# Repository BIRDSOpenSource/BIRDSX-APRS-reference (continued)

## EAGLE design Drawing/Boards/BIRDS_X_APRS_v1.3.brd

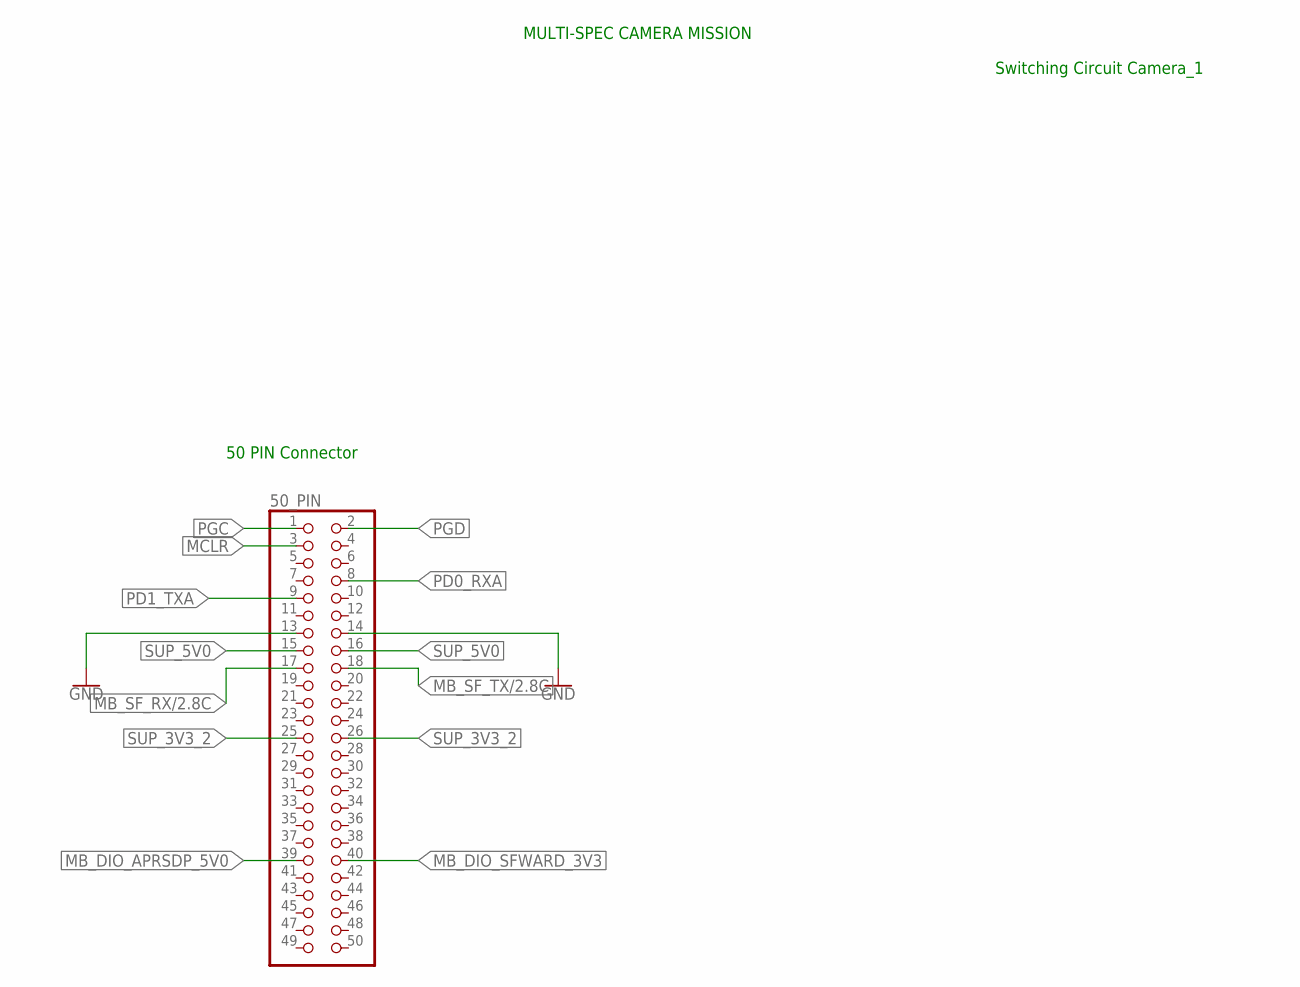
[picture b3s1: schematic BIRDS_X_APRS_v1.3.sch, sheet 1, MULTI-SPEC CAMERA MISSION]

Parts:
50_PIN: PINHD-2X25_2.00; 2X25M

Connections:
GND: 50_PIN.13, 50_PIN.14; also elsewhere on the board
MB_DIO_APRSDP_5V0: 50_PIN.39; also elsewhere on the board
MB_DIO_SFWARD_3V3: 50_PIN.40; also elsewhere on the board
MB_SF_RX/2.8C: 50_PIN.17
MB_SF_TX/2.8C: 50_PIN.18
MCLR: 50_PIN.3; also elsewhere on the board
PD0_RXA: 50_PIN.8; also elsewhere on the board
PD1_TXA: 50_PIN.9; also elsewhere on the board
PGC: 50_PIN.1; also elsewhere on the board
PGD: 50_PIN.2; also elsewhere on the board
SUP_3V3_2: 50_PIN.25, 50_PIN.26; also elsewhere on the board
SUP_5V0: 50_PIN.15, 50_PIN.16; also elsewhere on the board

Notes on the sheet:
50 PIN Connector
Switching Circuit Camera_1
MULTI-SPEC CAMERA MISSION

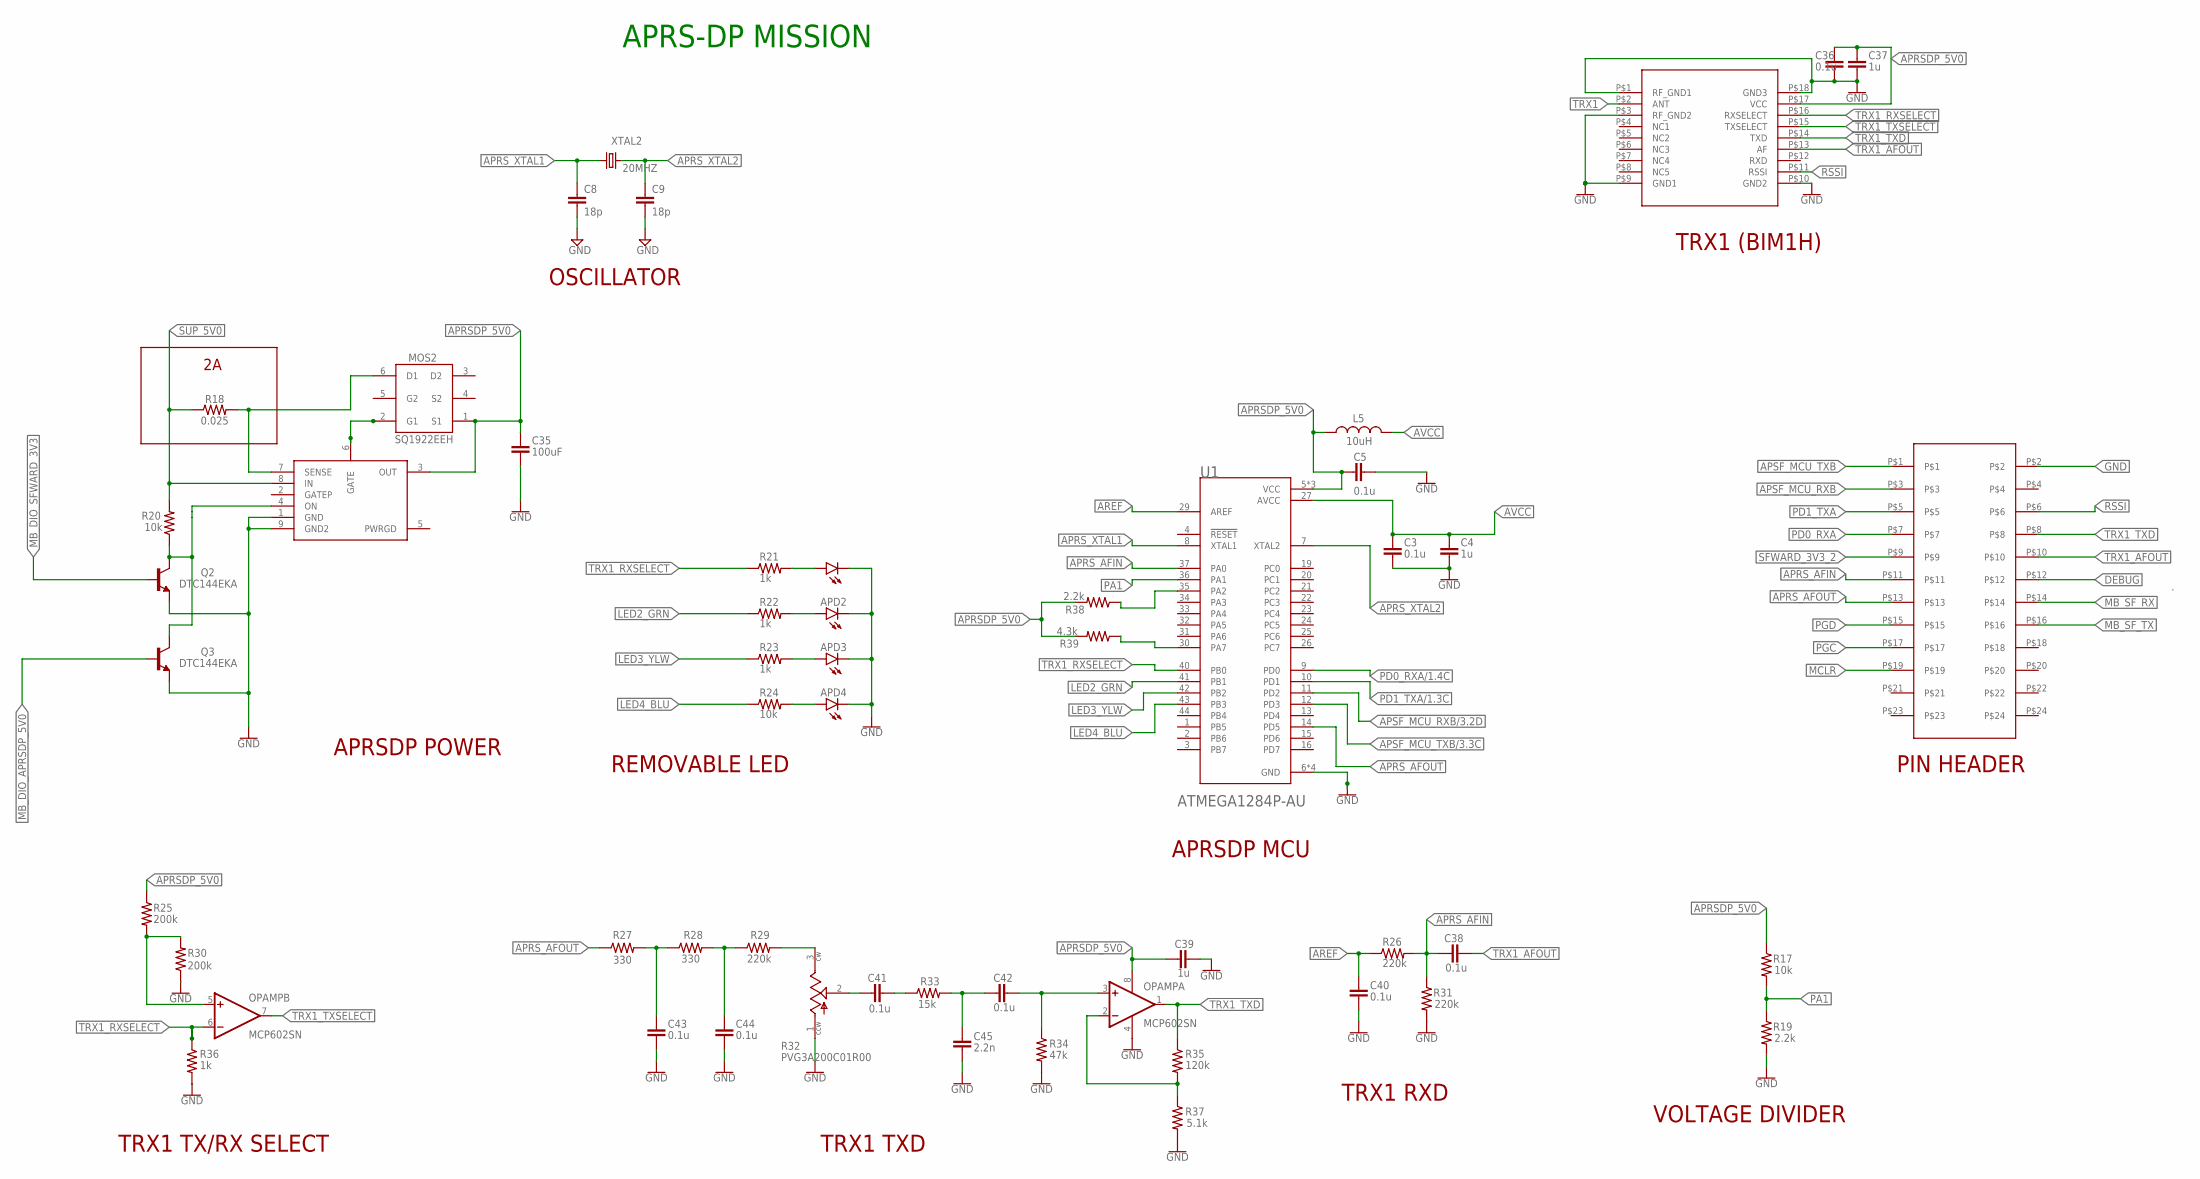
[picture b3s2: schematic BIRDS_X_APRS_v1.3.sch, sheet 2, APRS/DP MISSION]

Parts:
APD1, APD2, APD3, APD4: LEDSML0603; SML0603
C3, C5, C36, C38, C40, C41, C42, C43, C44: 0.1u; C0603
C4, C37, C39: 1u; C0603
C8, C9: 18p; C0805
C35: 100uF; C0805
C45: 2.2n; C0603
JP1: RAB_ACCESS
L5: 10uH; L2012C
MOS2: SQ1922EEH; SOT65P210X110-6N
OPAMP: MCP602SN; SO08
Q2, Q3: DTC144EKA; SOT346-R
R17, R20, R24: 10k; R0603
R18: 0.025; R0805
R19, R38: 2.2k; R0603
R21, R22, R23, R36: 1k; R0603
R25, R30: 200k; R0603
R26, R29, R31: 220k; R0603
R27, R28: 330; R0603
R32: PVG3A200C01R00; TRIM_PVG3A200C01R00
R33: 15k; R0603
R34: 47k; R0603
R35: 120k; R0603
R37: 5.1k; R0603
R39: 4.3k; R0603
TRX1: BIM1H
U1: ATMEGA1284P-AU; QFP80P1200X1200X120-44N
U$1: BIRDS5_LTC4361
XTAL2: 20MHZ; SM49

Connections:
APRSDP_5V0: C5.2, C35.1, C36.1, C37.1, C39.1, L5.1, MOS2.1 (S1), OPAMP.8 (V+), R17.1, R25.1, R38.2, R39.2, TRX1.P$17 (VCC), U1.5 (VCC), U1.17 (VCC), U1.38 (VCC), U$1.3 (OUT)
APRS_AFIN: C38.1, JP1.P$11, R26.2, R31.1, U1.37 (PA0)
APRS_AFOUT: JP1.P$13, R27.1, U1.14 (PD5)
APRS_XTAL1: C8.1, U1.8 (XTAL1), XTAL2.1
APRS_XTAL2: C9.1, U1.7 (XTAL2), XTAL2.2
APSF_MCU_RXB: JP1.P$3; also elsewhere on the board
APSF_MCU_RXB/3.2D: U1.11 (PD2)
APSF_MCU_TXB: JP1.P$1; also elsewhere on the board
APSF_MCU_TXB/3.3C: U1.12 (PD3)
AREF: C40.1, R26.1, U1.29 (AREF)
AVCC: C3.1, C4.1, L5.2, U1.27 (AVCC)
DEBUG: JP1.P$12; also elsewhere on the board
GATE4: MOS2.2 (G1), U$1.6 (GATE)
GND: APD1.C, APD2.C, APD3.C, APD4.C, C3.2, C4.2, C5.1, C8.2, C9.2, C35.2, C36.2, C37.2, C39.2, C40.2, C43.2, C44.2, C45.2, JP1.P$2, OPAMP.4 (V-), Q2.1 (E), Q3.1 (E), R19.2, R30.1, R31.2, R32.1 (CCW), R34.2, R36.2, R37.2, TRX1.P$1 (RF_GND1), TRX1.P$3 (RF_GND2), TRX1.P$9 (GND1), TRX1.P$10 (GND2), TRX1.P$18 (GND3), U1.6 (GND), U1.18 (GND), U1.28 (GND), U1.39 (GND), U$1.1 (GND), U$1.9 (GND2); also elsewhere on the board
LED2_GRN: R22.1, U1.41 (PB1)
LED3_YLW: R23.1, U1.42 (PB2)
LED4_BLU: R24.1, U1.43 (PB3)
MB_DIO_APRSDP_5V0: Q3.2 (B); also elsewhere on the board
MB_DIO_SFWARD_3V3: Q2.2 (B); also elsewhere on the board
MB_SF_RX: JP1.P$14; also elsewhere on the board
MB_SF_TX: JP1.P$16; also elsewhere on the board
MCLR: JP1.P$19; also elsewhere on the board
unnamed: R38.1, U1.35 (PA2)
unnamed: R39.1, U1.30 (PA7)
unnamed: R29.2, R32.3 (CW)
unnamed: APD1.A, R21.2
unnamed: APD2.A, R22.2
unnamed: APD3.A, R23.2
unnamed: APD4.A, R24.2
unnamed: C43.1, R27.2, R28.1
unnamed: C44.1, R28.2, R29.1
unnamed: C42.1, C45.1, R33.2
unnamed: C41.2, R33.1
unnamed: OPAMP.2 (-IN), R35.2, R37.1
unnamed: OPAMP.5 (+IN), R25.2, R30.2
unnamed: C41.1, R32.2 (WIPER)
ON4: Q2.3 (C), Q3.3 (C), R20.1, U$1.4 (ON)
OPAMP_A+: C42.2, OPAMP.3 (+IN), R34.1
PA1: R17.2, R19.1, U1.36 (PA1)
PD0_RXA: JP1.P$7; also elsewhere on the board
PD0_RXA/1.4C: U1.9 (PD0)
PD1_TXA: JP1.P$5; also elsewhere on the board
PD1_TXA/1.3C: U1.10 (PD1)
PGC: JP1.P$17; also elsewhere on the board
PGD: JP1.P$15; also elsewhere on the board
RSSI: JP1.P$6, TRX1.P$11 (RSSI); also elsewhere on the board
SENSE4: MOS2.6 (D1), R18.2, U$1.7 (SENSE)
SFWARD_3V3_2: JP1.P$9; also elsewhere on the board
SUP_5V0: R18.1, R20.2, U$1.8 (IN); also elsewhere on the board
TRX1: TRX1.P$2 (ANT); also elsewhere on the board
TRX1_AFOUT: C38.2, JP1.P$10, TRX1.P$13 (AF)
TRX1_RXSELECT: OPAMP.6 (-IN), R21.1, R36.1, TRX1.P$16 (RXSELECT), U1.40 (PB0)
TRX1_TXD: JP1.P$8, OPAMP.1 (OUT), R35.1, TRX1.P$14 (TXD)
TRX1_TXSELECT: OPAMP.7 (OUT), TRX1.P$15 (TXSELECT)

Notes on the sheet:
OSCILLATOR
APRSDP POWER
PIN HEADER
TRX1 RXD
TRX1 (BIM1H)
VOLTAGE DIVIDER
REMOVABLE LED
APRS-DP MISSION
APRSDP MCU
TRX1 TXD
TRX1 TX/RX SELECT

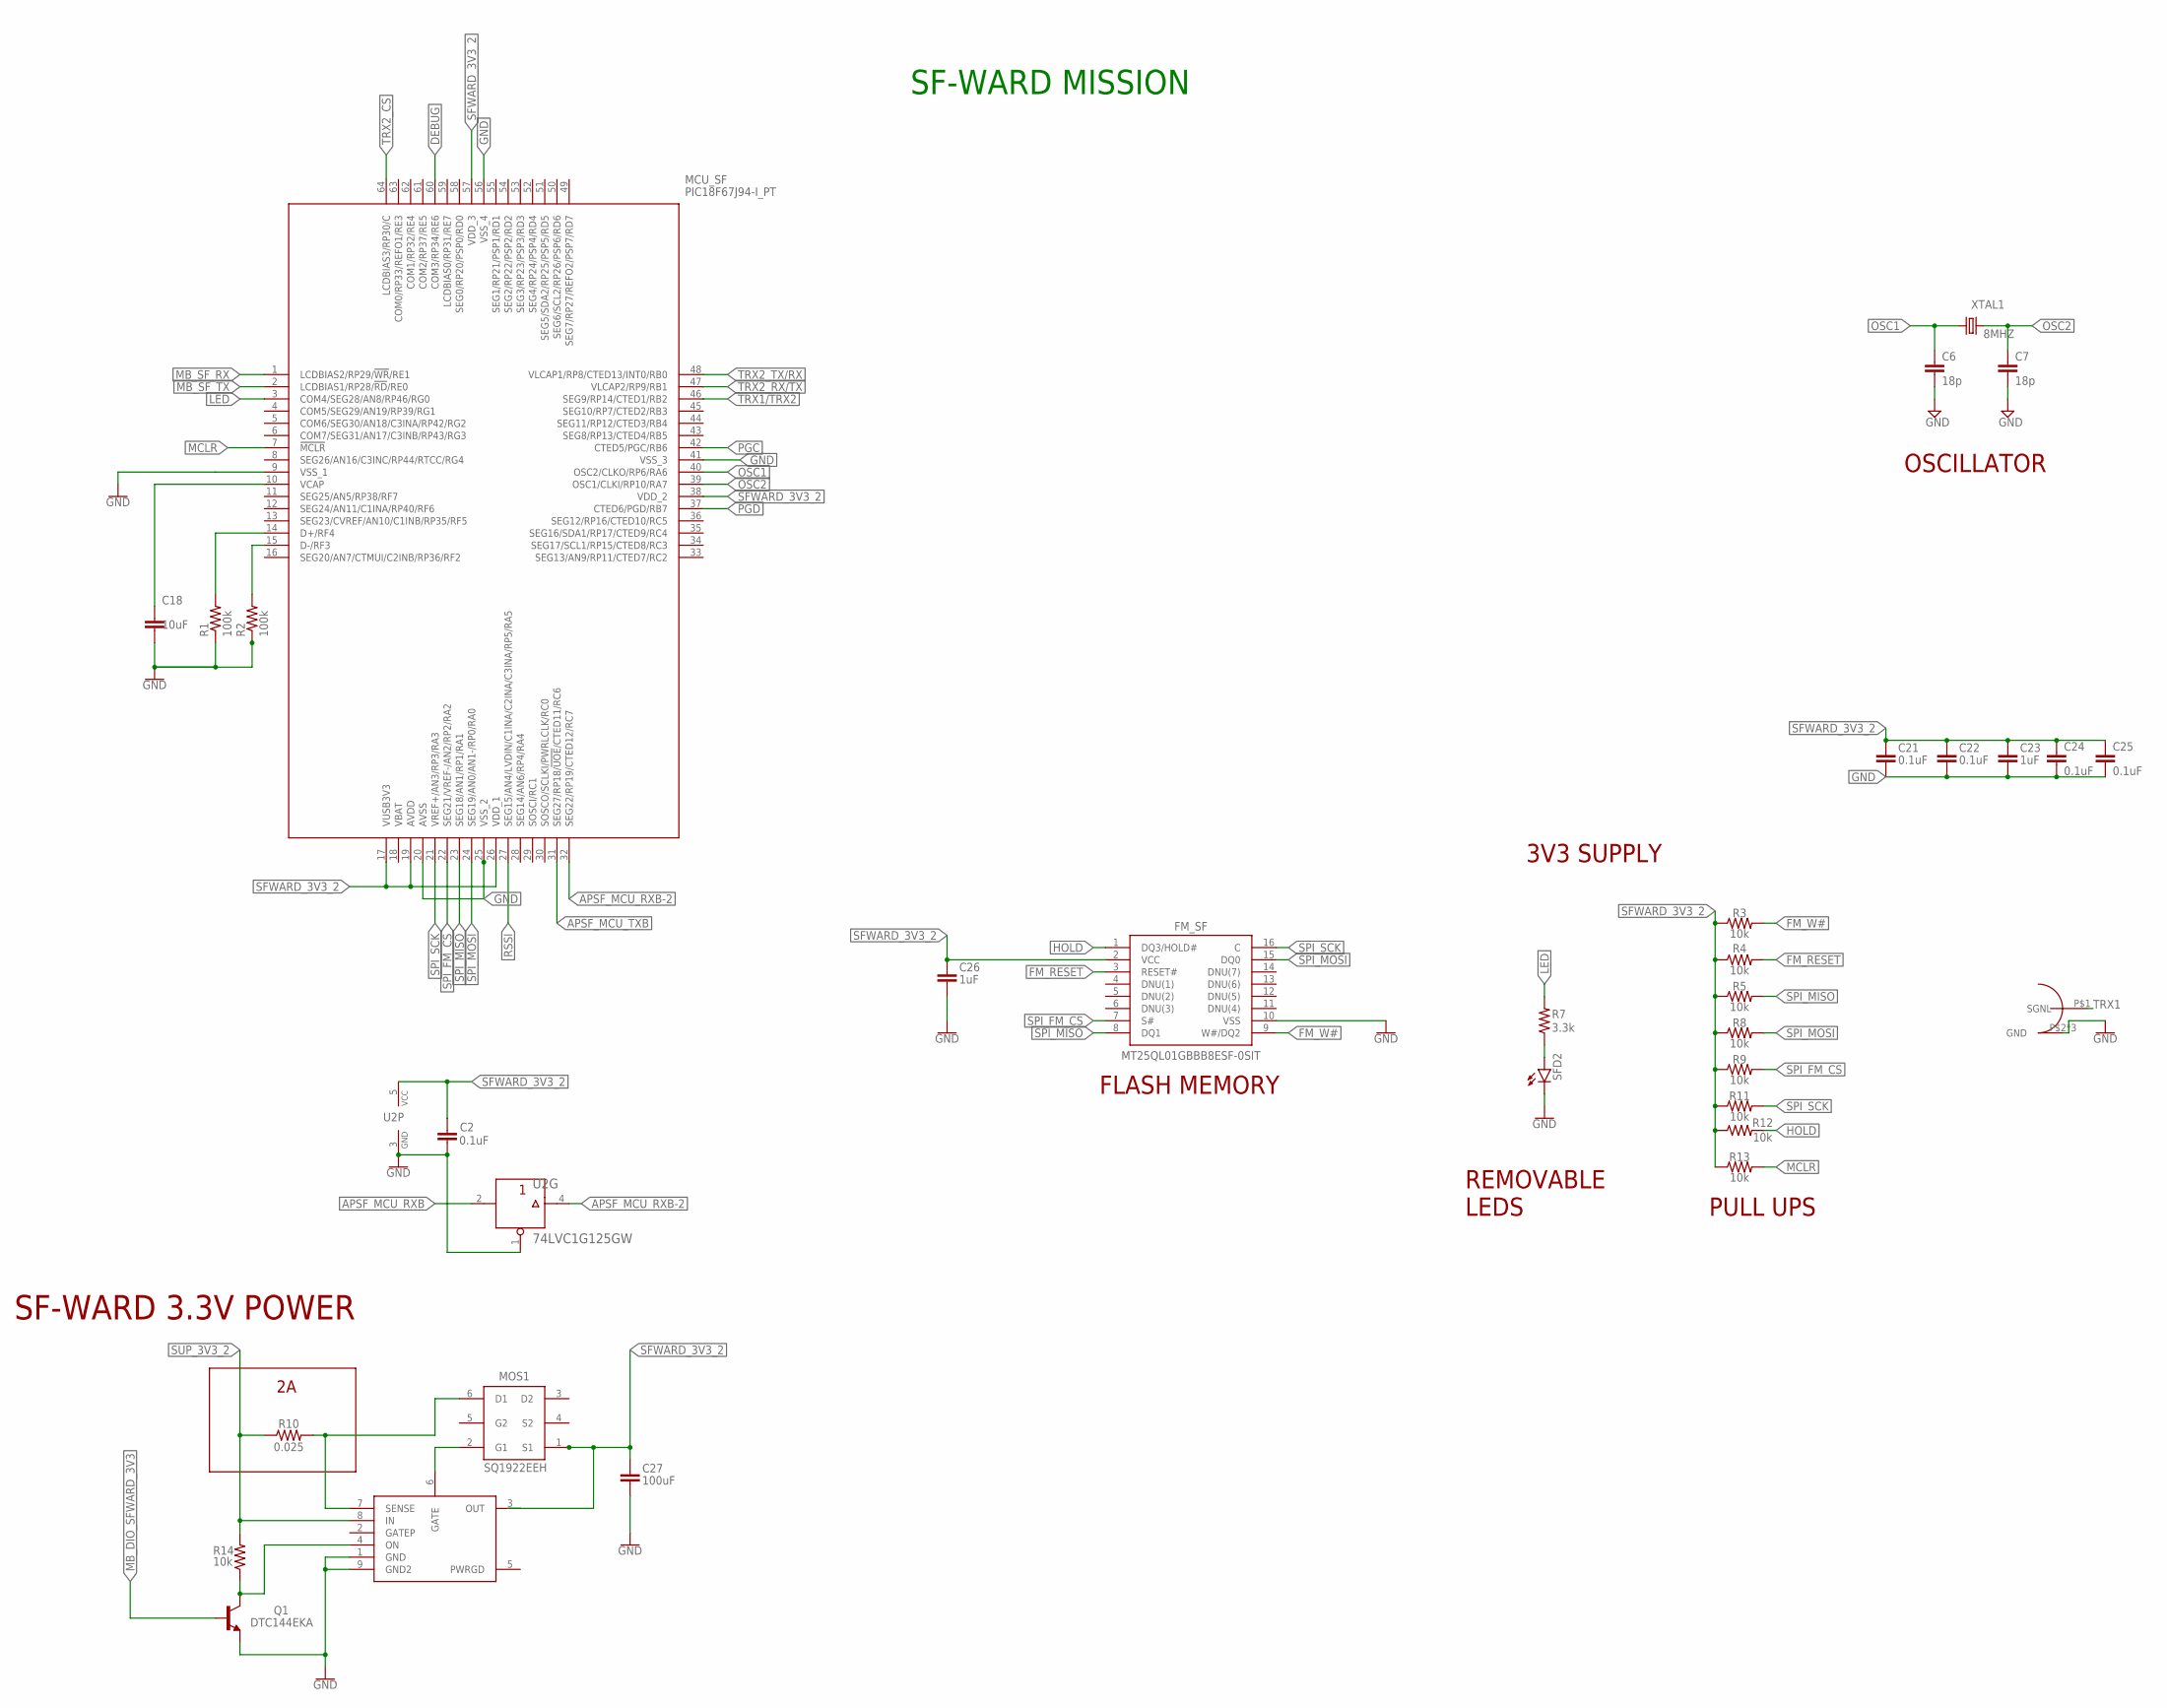
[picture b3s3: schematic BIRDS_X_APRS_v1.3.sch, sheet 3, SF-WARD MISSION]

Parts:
C2, C21, C22, C24, C25: 0.1uF; C0603
C6, C7: 18p; C0805
C18: 10uF; C0603
C23, C26: 1uF; C0603
C27: 100uF; C0805
FM_SF: MT25QL01GBBB8ESF-0SIT; SOIC127P1032X265-16N
MCU_SF: PIC18F67J94-I_PT; QFP50P1200X1200X120-64N
MMCX_908_222101T: MMCX_908_222101T
MOS1: SQ1922EEH; SOT65P210X110-6N
Q1: DTC144EKA; SOT346-R
R1, R2: 100k; R0603
R3, R4, R5, R8, R9, R11, R12, R13, R14: 10k; R0603
R7: 3.3k; R0603
R10: 0.025; R0805
SFD2: LEDCHIPLED_0603; CHIPLED_0603
U2: 74LVC1G125GW; SOT353-1
U$3: BIRDS5_LTC4361
XTAL1: 8MHZ; SM49

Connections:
APSF_MCU_RXB: U2.2 (A); also elsewhere on the board
APSF_MCU_RXB-2: MCU_SF.32 (SEG22/RP19/CTED12/RC7), U2.4 (Y)
APSF_MCU_TXB: MCU_SF.31 (SEG27/RP18/!UOE!/CTED11/RC6); also elsewhere on the board
DEBUG: MCU_SF.60 (COM3/RP34/RE6); also elsewhere on the board
FM_RESET: FM_SF.3 (RESET#), R4.2
FM_W#: FM_SF.9 (W#/DQ2), R3.2
GATE3: MOS1.2 (G1), U$3.6 (GATE)
GND: C2.1, C6.2, C7.2, C18.2, C21.2, C22.2, C23.2, C24.2, C25.2, C26.2, C27.2, FM_SF.10 (VSS), MCU_SF.9 (VSS_1), MCU_SF.20 (AVSS), MCU_SF.25 (VSS_2), MCU_SF.41 (VSS_3), MCU_SF.56 (VSS_4), MMCX_908_222101T.P$2 (GND), MMCX_908_222101T.P$3 (GND), MMCX_908_222101T.P$4 (GND), Q1.1 (E), R1.1, R2.1, SFD2.C, U2.1 (OEN), U2.3 (GND), U$3.1 (GND), U$3.9 (GND2); also elsewhere on the board
HOLD: FM_SF.1 (DQ3/HOLD#), R12.2
LED: MCU_SF.3 (COM4/SEG28/AN8/RP46/RG0), R7.2
MB_DIO_SFWARD_3V3: Q1.2 (B); also elsewhere on the board
MB_SF_RX: MCU_SF.1 (LCDBIAS2/RP29/!WR!/RE1); also elsewhere on the board
MB_SF_TX: MCU_SF.2 (LCDBIAS1/RP28/!RD!/RE0); also elsewhere on the board
MCLR: MCU_SF.7 (!MCLR), R13.2; also elsewhere on the board
unnamed: C18.1, MCU_SF.10 (VCAP)
unnamed: MCU_SF.14 (D+/RF4), R1.2
unnamed: MCU_SF.15 (D-/RF3), R2.2
unnamed: R7.1, SFD2.A
ON3: Q1.3 (C), R14.1, U$3.4 (ON)
OSC1: C6.1, MCU_SF.40 (OSC2/CLKO/RP6/RA6), XTAL1.1
OSC2: C7.1, MCU_SF.39 (OSC1/CLKI/RP10/RA7), XTAL1.2
PGC: MCU_SF.42 (CTED5/PGC/RB6); also elsewhere on the board
PGD: MCU_SF.37 (CTED6/PGD/RB7); also elsewhere on the board
RSSI: MCU_SF.27 (SEG15/AN4/LVDIN/C1INA/C2INA/C3INA/RP5/R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); also elsewhere on the board
SENSE3: MOS1.6 (D1), R10.2, U$3.7 (SENSE)
SFWARD_3V3_2: C2.2, C21.1, C22.1, C23.1, C24.1, C25.1, C26.1, C27.1, FM_SF.2 (VCC), MCU_SF.17 (VUSB3V3), MCU_SF.19 (AVDD), MCU_SF.26 (VDD_1), MCU_SF.38 (VDD_2), MCU_SF.57 (VDD_3), MOS1.1 (S1), R3.1, R4.1, R5.1, R8.1, R9.1, R11.1, R12.1, R13.1, U2.5 (VCC), U$3.3 (OUT); also elsewhere on the board
SPI_FM_CS: FM_SF.7 (S#), MCU_SF.22 (SEG21/VREF-/AN2/RP2/RA2), R9.2
SPI_MISO: FM_SF.8 (DQ1), MCU_SF.23 (SEG18/AN1/RP1/RA1), R5.2
SPI_MOSI: FM_SF.15 (DQ0), MCU_SF.24 (SEG19/AN0/AN1-/RP0/RA0), R8.2
SPI_SCK: FM_SF.16 (C), MCU_SF.21 (VREF+/AN3/RP3/RA3), R11.2
SUP_3V3_2: R10.1, R14.2, U$3.8 (IN); also elsewhere on the board
TRX1: MMCX_908_222101T.P$1 (SGNL); also elsewhere on the board
TRX1/TRX2: MCU_SF.46 (SEG9/RP14/CTED1/RB2)
TRX2_CS: MCU_SF.64 (LCDBIAS3/RP30/C)
TRX2_RX/TX: MCU_SF.47 (VLCAP2/RP9/RB1)
TRX2_TX/RX: MCU_SF.48 (VLCAP1/RP8/CTED13/INT0/RB0)

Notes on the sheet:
FLASH MEMORY
SF-WARD 3.3V POWER
PULL UPS
REMOVABLE LEDS
OSCILLATOR
3V3 SUPPLY
SF-WARD MISSION

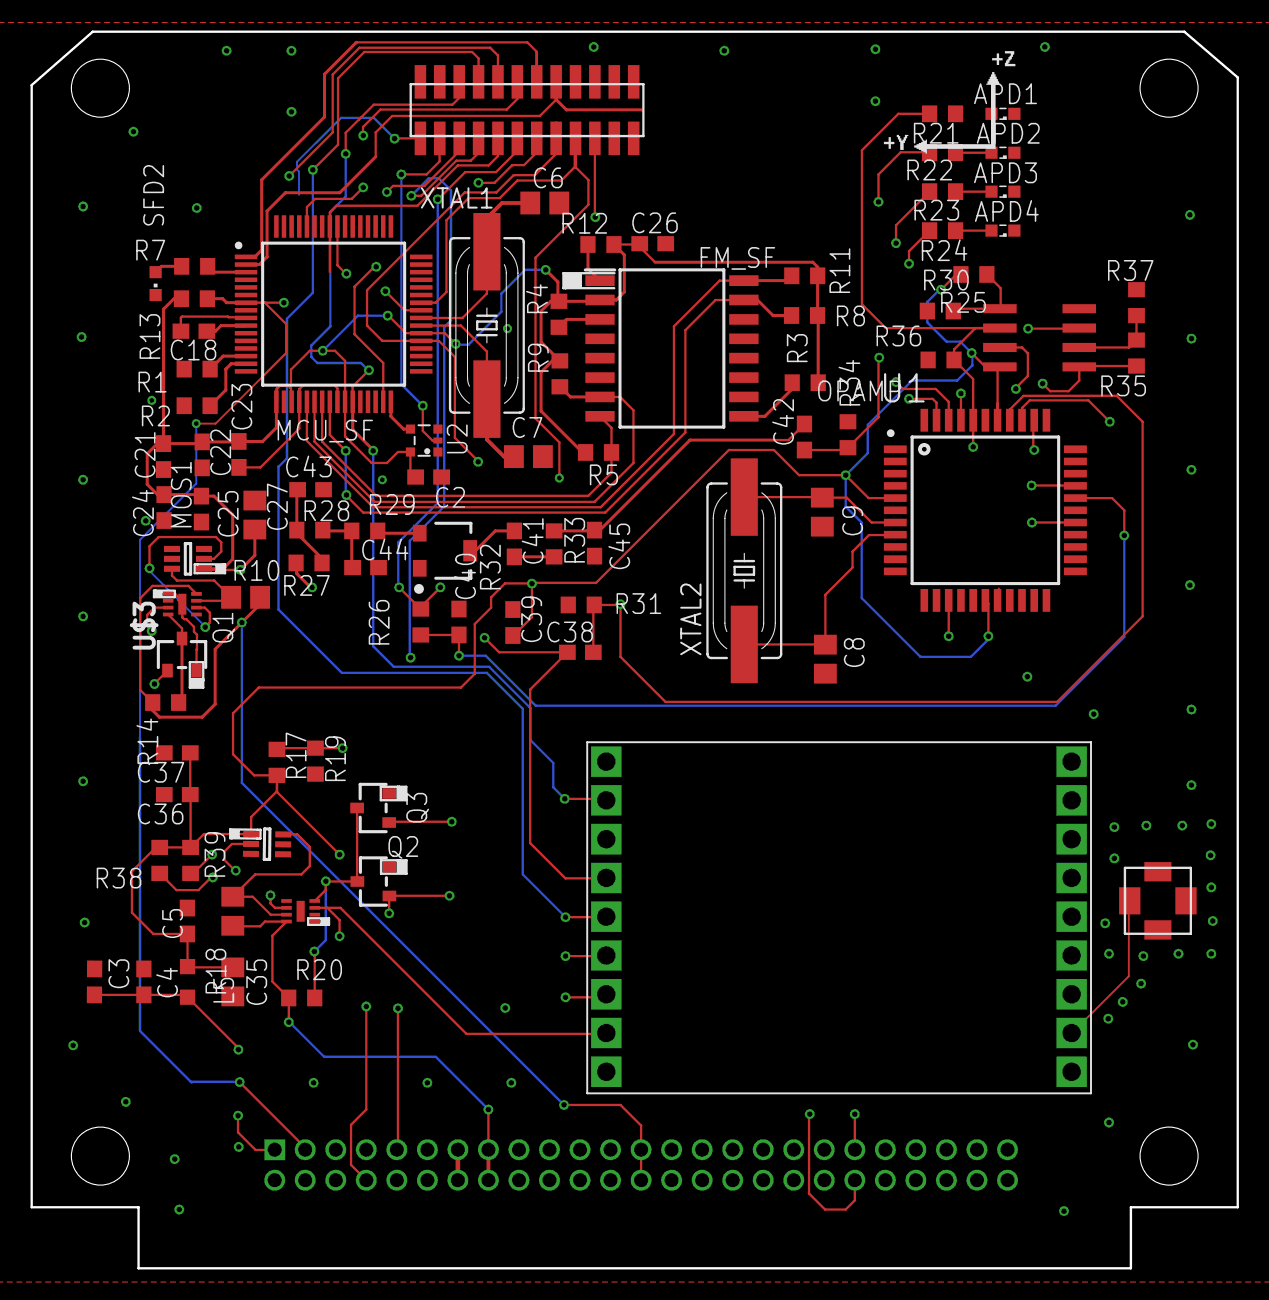
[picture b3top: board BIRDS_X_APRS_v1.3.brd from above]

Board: 4 copper layers, 79.0 x 81.0 mm, 87 parts (1 on the bottom side), 69 nets.

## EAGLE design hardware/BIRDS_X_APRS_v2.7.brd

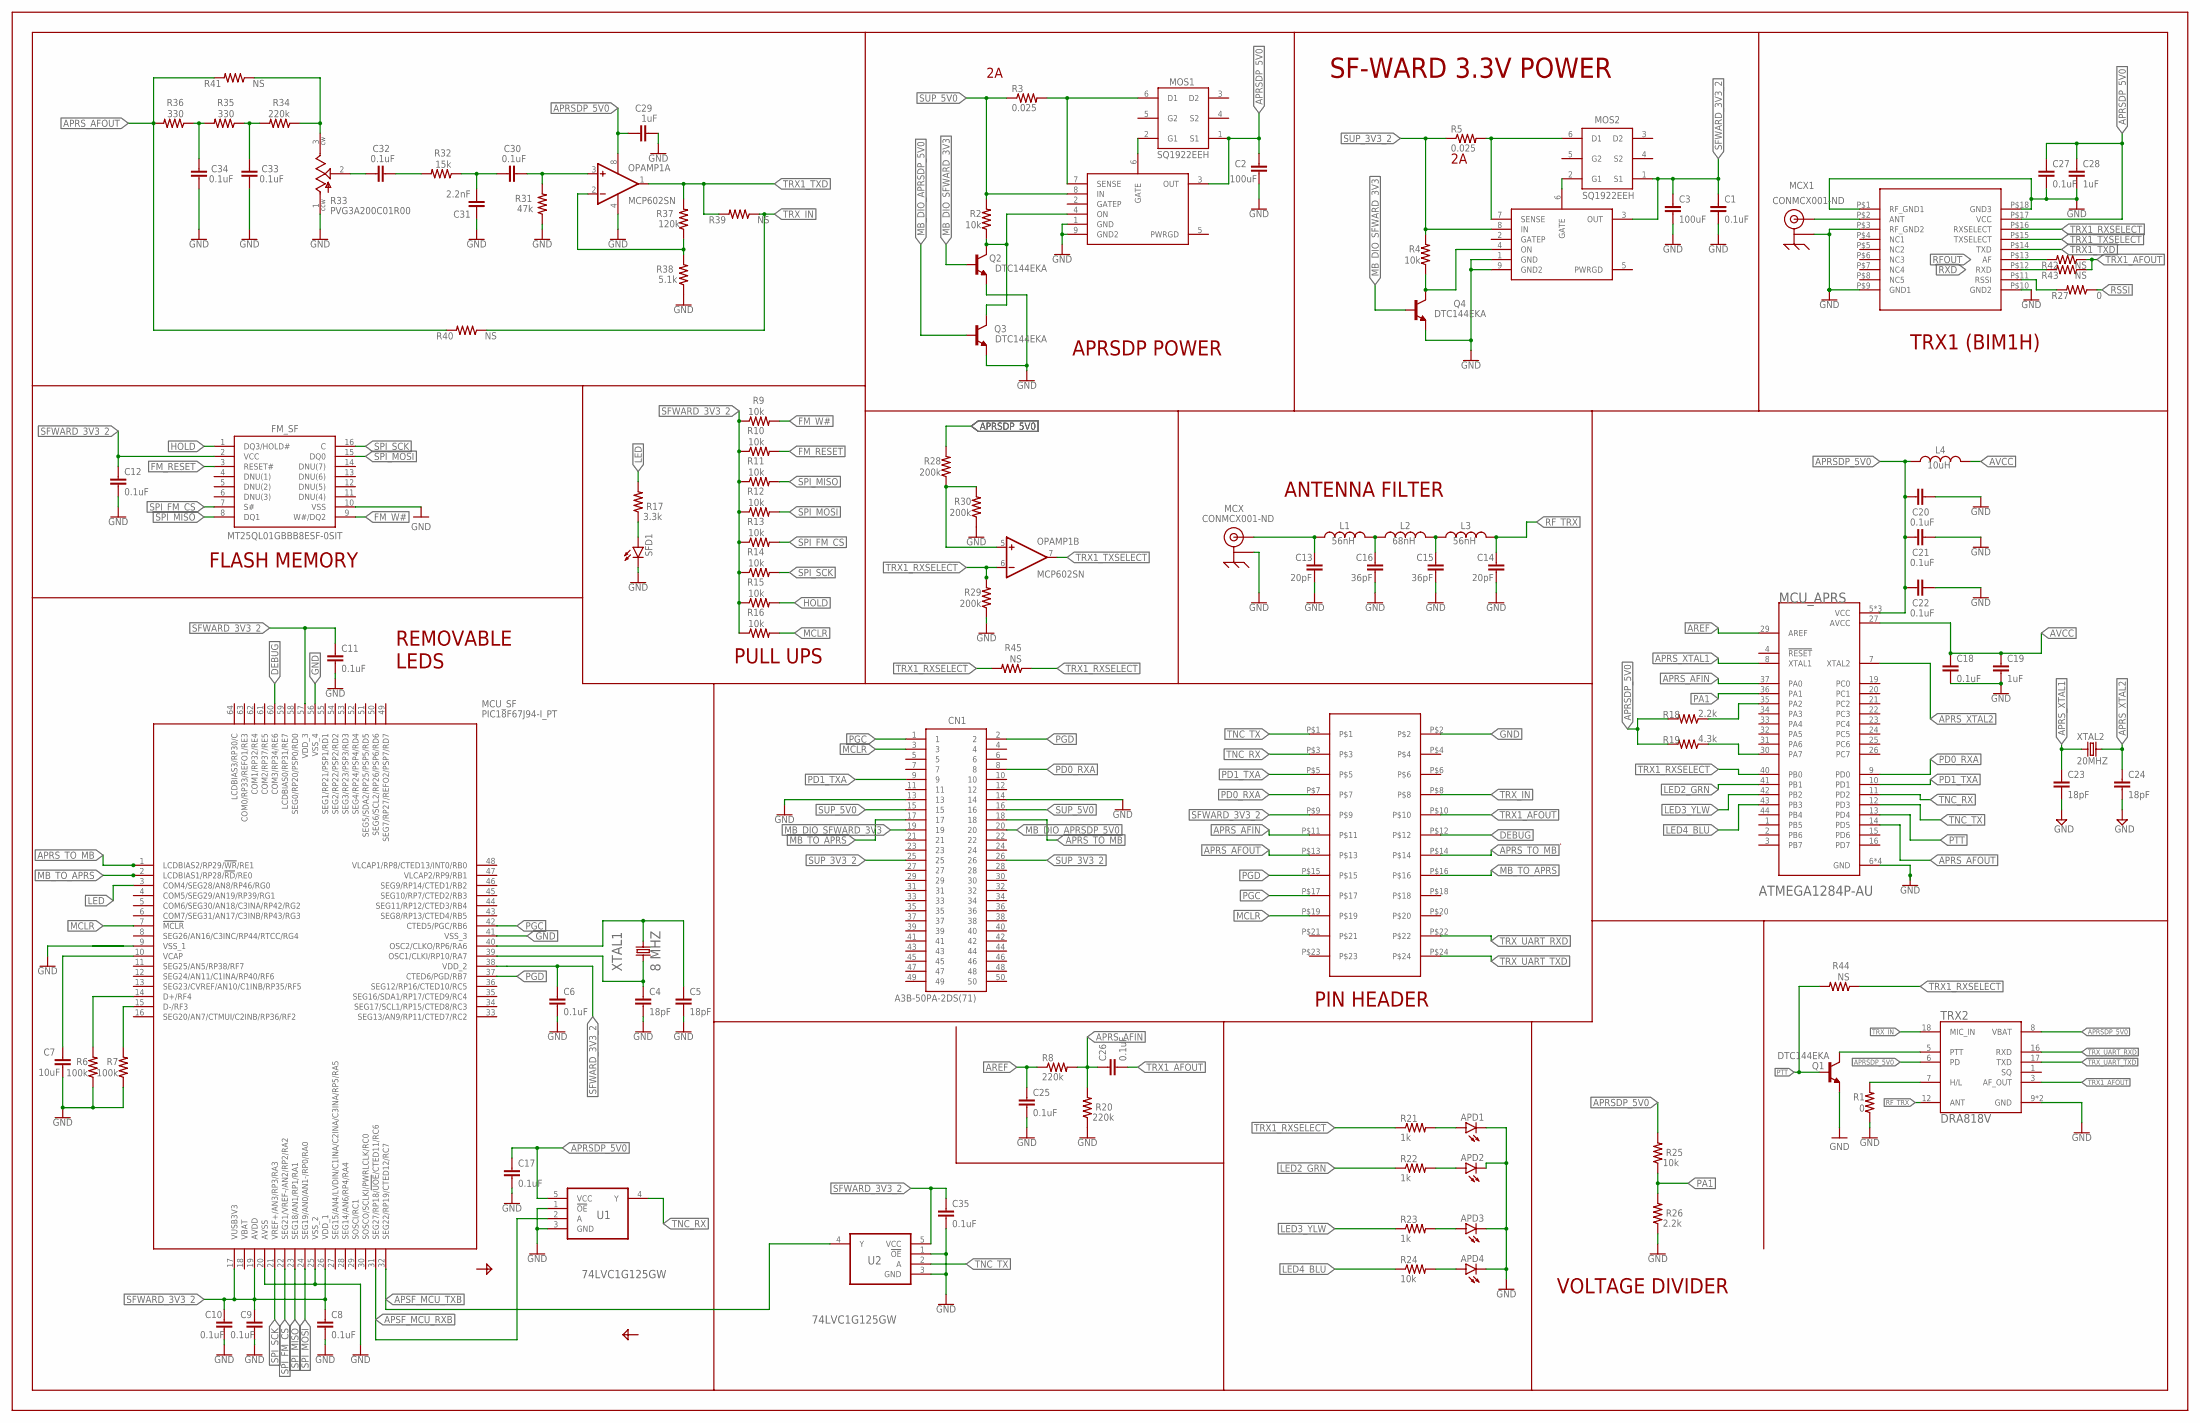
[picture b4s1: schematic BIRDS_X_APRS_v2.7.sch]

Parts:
APD1, APD2, APD3, APD4: LEDSML0603; SML0603
C1, C6, C8, C9, C10, C11, C12, C17, C18, C20, C21, C22, C25, C26, C27, C30, C32, C33, C34, C35: 0.1uF; M(1005)_US(0402)
C2, C3: 100uF; M(2012)_US(0805)
C4, C5, C23, C24: 18pF; M(1005)_US(0402)
C7: 10uF; M(1608)_US(0603)
C13, C14: 20pF; M(1608)_US(0603)
C15, C16: 36pF; M(1608)_US(0603)
C19, C28, C29: 1uF; M(1005)_US(0402)
C31: 2.2nF; M(1005)_US(0402)
CN1: A3B-50PA-2DS(71)
FM_SF: MT25QL01GBBB8ESF-0SIT; SOIC127P1032X265-16N
JP1: RAB_ACCESS
L1, L3: 56nH; M(2012)_US(0805)
L2: 68nH; M(2012)_US(0805)
L4: 10uH; M(2012)_US(0805)
MCU_APRS: ATMEGA1284P-AU; QFP80P1200X1200X120-44N
MCU_SF: PIC18F67J94-I_PT; QFP50P1200X1200X120-64N
MCX, MCX1: CONMCX001-ND
MOS1, MOS2: SQ1922EEH; SOT65P210X110-6N
OCP1, OCP2: BIRDS5_LTC4361
OPAMP1: MCP602SN; SO08
Q1, Q2, Q3, Q4: DTC144EKA; SOT346-R
R1: 0; M(1005)_US(0402)
R2, R4, R9, R10, R11, R12, R13, R14, R15, R16: 10k; M(1005)_US(0402)
R3, R5: 0.025; M(2012)_US(0805)
R6, R7: 100k; M(1005)_US(0402)
R8, R20, R34: 220k; M(1608)_US(0603)
R17: 3.3k; M(1608)_US(0603)
R18: 2.2k; M(1005)_US(0402)
R19: 4.3k; M(1005)_US(0402)
R21, R22, R23: 1k; M(1608)_US(0603)
R24, R25: 10k; M(1608)_US(0603)
R26: 2.2k; M(1608)_US(0603)
R27: 0; M(1608)_US(0603)
R28, R29, R30: 200k; M(1005)_US(0402)
R31: 47k; M(1608)_US(0603)
R32: 15k; M(1608)_US(0603)
R33: PVG3A200C01R00; TRIM_PVG3A200C01R00
R35, R36: 330; M(1608)_US(0603)
R37: 120k; M(1608)_US(0603)
R38: 5.1k; M(1608)_US(0603)
R39, R40, R41, R42, R43, R44, R45: NS; M(1608)_US(0603)
SFD1: LEDCHIPLED_0603; CHIPLED_0603
TRX1: BIM1H
TRX2: DRA818V; DORJI_DRA818V
U1, U2: 74LVC1G125GW; SOT65P210X110-5N
XTAL1: 8 MHZ; CRYSTAL_SM49
XTAL2: 20MHZ; SM49

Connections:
APRSDP_5V0: C2.1, C17.1, C20.1, C21.1, C22.1, C27.1, C28.1, C29.1, L4.1, MCU_APRS.5 (VCC), MCU_APRS.17 (VCC), MCU_APRS.38 (VCC), MOS1.1 (S1), OCP1.3 (OUT), OPAMP1.8 (V+), R18.2, R19.2, R25.2, R28.2, TRX1.P$17 (VCC), TRX2.6 (PD), TRX2.8 (VBAT), U1.5 (VCC)
APRS_AFIN: C26.1, JP1.P$11, MCU_APRS.37 (PA0), R8.2, R20.2
APRS_AFOUT: JP1.P$13, MCU_APRS.14 (PD5), R36.2, R40.2, R41.2
APRS_TO_MB: CN1.18, JP1.P$14, MCU_SF.1 (LCDBIAS2/RP29/!WR!/RE1)
APRS_XTAL1: C23.1, MCU_APRS.8 (XTAL1), XTAL2.1
APRS_XTAL2: C24.1, MCU_APRS.7 (XTAL2), XTAL2.2
APSF_MCU_RXB: MCU_SF.31 (SEG27/RP18/!UOE!/CTED11/RC6), U1.2 (A)
APSF_MCU_TXB: MCU_SF.32 (SEG22/RP19/CTED12/RC7), U2.4 (Y)
AREF: C25.1, MCU_APRS.29 (AREF), R8.1
AVCC: C18.1, C19.1, L4.2, MCU_APRS.27 (AVCC)
DEBUG: JP1.P$12, MCU_SF.60 (COM3/RP34/RE6)
FM_RESET: FM_SF.3 (RESET#), R10.2
FM_W#: FM_SF.9 (W#/DQ2), R9.2
GATE3: MOS2.2 (G1), OCP2.6 (GATE)
GND: APD1.C, APD2.C, APD3.C, APD4.C, C1.2, C2.2, C3.2, C4.2, C5.2, C6.2, C7.2, C8.2, C9.2, C10.2, C11.2, C12.2, C13.2, C14.2, C15.2, C16.2, C17.2, C18.2, C19.2, C20.2, C21.2, C22.2, C23.2, C24.2, C25.2, C27.2, C28.2, C29.2, C31.1, C33.2, C34.2, C35.2, CN1.13, CN1.14, FM_SF.10 (VSS), JP1.P$2, MCU_APRS.6 (GND), MCU_APRS.18 (GND), MCU_APRS.28 (GND), MCU_APRS.39 (GND), MCU_SF.9 (VSS_1), MCU_SF.20 (AVSS), MCU_SF.25 (VSS_2), MCU_SF.41 (VSS_3), MCU_SF.56 (VSS_4), MCX.2, MCX.3 (2), MCX.4 (2), MCX.5 (2), MCX1.2, MCX1.3 (2), MCX1.4 (2), MCX1.5 (2), OCP1.1 (GND), OCP1.9 (GND2), OCP2.1 (GND), OCP2.9 (GND2), OPAMP1.4 (V-), Q1.1 (E), Q2.1 (E), Q3.1 (E), Q4.1 (E), R1.1, R20.1, R26.1, R30.1, R31.1, R33.1 (CCW), R38.1, TRX1.P$1 (RF_GND1), TRX1.P$3 (RF_GND2), TRX1.P$9 (GND1), TRX1.P$10 (GND2), TRX1.P$18 (GND3), TRX2.9 (GND), TRX2.10 (GND), U1.1 (!OE), U1.3 (GND), U2.1 (!OE), U2.3 (GND)
HOLD: FM_SF.1 (DQ3/HOLD#), R15.2
LED: MCU_SF.3 (COM4/SEG28/AN8/RP46/RG0), R17.2
LED2_GREEN: APD2.A, R22.2
LED2_GRN: MCU_APRS.41 (PB1), R22.1
LED3_YLW: MCU_APRS.42 (PB2), R23.1
LED4_BLU: MCU_APRS.43 (PB3), R24.1
LED4_BLUE: APD4.A, R24.2
LED_3_YELLOW: APD3.A, R23.2
MB_DIO_APRSDP_5V0: CN1.20, Q3.2 (B)
MB_DIO_SFWARD_3V3: CN1.19, Q2.2 (B), Q4.2 (B)
MB_TO_APRS: CN1.17, JP1.P$16, MCU_SF.2 (LCDBIAS1/RP28/!RD!/RE0)
MCLR: CN1.3, JP1.P$19, MCU_SF.7 (!MCLR), R16.2
unnamed: MOS1.2 (G1), OCP1.6 (GATE)
unnamed: C7.1, MCU_SF.10 (VCAP)
unnamed: C5.1, MCU_SF.40 (OSC2/CLKO/RP6/RA6), XTAL1.2
unnamed: MCU_SF.15 (D-/RF3), R7.2
unnamed: MCU_SF.14 (D+/RF4), R6.2
unnamed: R17.1, SFD1.A
unnamed: C15.1, L2.2, L3.1
unnamed: C16.1, L1.2, L2.1
unnamed: C13.1, L1.1, MCX.1
unnamed: R1.2, TRX2.7 (H/L)
unnamed: MCU_APRS.35 (PA2), R18.1
unnamed: MCU_APRS.30 (PA7), R19.1
unnamed: R27.2, TRX1.P$11 (RSSI)
unnamed: MCX1.1, TRX1.P$2 (ANT)
unnamed: OPAMP1.5 (+IN), R28.1, R30.2
unnamed: C32.2, R32.2
unnamed: C30.1, C31.2, R32.1
unnamed: C30.2, OPAMP1.3 (+IN), R31.2
unnamed: Q1.3 (C), TRX2.5 (PTT)
unnamed: C32.1, R33.2 (WIPER)
unnamed: R33.3 (CW), R34.1, R41.1
unnamed: C34.1, R35.2, R36.1
unnamed: C33.1, R34.2, R35.1
unnamed: OPAMP1.2 (-IN), R37.1, R38.2
ON3: OCP2.4 (ON), Q4.3 (C), R4.1
ON4: OCP1.4 (ON), Q2.3 (C), Q3.3 (C), R2.1
OSC2: C4.1, MCU_SF.39 (OSC1/CLKI/RP10/RA7), XTAL1.1
PA1: MCU_APRS.36 (PA1), R25.1, R26.2
PD0_RXA: CN1.8, JP1.P$7, MCU_APRS.9 (PD0)
PD1_TXA: CN1.9, JP1.P$5, MCU_APRS.10 (PD1)
PGC: CN1.1, JP1.P$17, MCU_SF.42 (CTED5/PGC/RB6)
PGD: CN1.2, JP1.P$15, MCU_SF.37 (CTED6/PGD/RB7)
PTT: MCU_APRS.13 (PD4), Q1.2 (B), R44.2
RFOUT: R42.2, TRX1.P$13 (AF)
RF_TRX: C14.1, L3.2, TRX2.12 (ANT)
RSSI: R27.1
RXD: R43.2, TRX1.P$12 (RXD)
SENSE3: MOS2.6 (D1), OCP2.7 (SENSE), R5.2
SENSE4: MOS1.6 (D1), OCP1.7 (SENSE), R3.2
SFWARD_3V3_2: C1.1, C3.1, C6.1, C8.1, C9.1, C10.1, C11.1, C12.1, C35.1, FM_SF.2 (VCC), JP1.P$9, MCU_SF.17 (VUSB3V3), MCU_SF.19 (AVDD), MCU_SF.26 (VDD_1), MCU_SF.38 (VDD_2), MCU_SF.57 (VDD_3), MOS2.1 (S1), OCP2.3 (OUT), R9.1, R10.1, R11.1, R12.1, R13.1, R14.1, R15.1, R16.1, U2.5 (VCC)
SPI_FM_CS: FM_SF.7 (S#), MCU_SF.22 (SEG21/VREF-/AN2/RP2/RA2), R13.2
SPI_MISO: FM_SF.8 (DQ1), MCU_SF.23 (SEG18/AN1/RP1/RA1), R11.2
SPI_MOSI: FM_SF.15 (DQ0), MCU_SF.24 (SEG19/AN0/AN1-/RP0/RA0), R12.2
SPI_SCK: FM_SF.16 (C), MCU_SF.21 (VREF+/AN3/RP3/RA3), R14.2
SUP_3V3_2: CN1.25, CN1.26, OCP2.8 (IN), R4.2, R5.1
SUP_5V0: CN1.15, CN1.16, OCP1.8 (IN), R2.2, R3.1
TNC_RX: JP1.P$3, MCU_APRS.11 (PD2), U1.4 (Y)
TNC_TX: JP1.P$1, MCU_APRS.12 (PD3), U2.2 (A)
TRX1_AFOUT: C26.2, JP1.P$10, R42.1, R43.1, TRX2.3 (AF_OUT)
TRX1_RXSELECT: MCU_APRS.40 (PB0), OPAMP1.6 (-IN), R21.1, R29.2, R44.1, R45.1, R45.2, TRX1.P$16 (RXSELECT)
TRX1_RX_LED: APD1.A, R21.2
TRX1_TXD: OPAMP1.1 (OUT), R37.2, R39.2, TRX1.P$14 (TXD)
TRX1_TXSELECT: OPAMP1.7 (OUT), TRX1.P$15 (TXSELECT)
TRX_IN: JP1.P$8, R39.1, R40.1, TRX2.18 (MIC_IN)
TRX_UART_RXD: JP1.P$22, TRX2.16 (RXD)
TRX_UART_TXD: JP1.P$24, TRX2.17 (TXD)

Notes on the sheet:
APRSDP POWER
SF-WARD 3.3V POWER
FLASH MEMORY
PULL UPS
REMOVABLE LEDS
ANTENNA FILTER
PIN HEADER
VOLTAGE DIVIDER
TRX1 (BIM1H)
